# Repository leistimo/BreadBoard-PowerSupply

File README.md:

# Breadboard-Powersupply 
## Fixed 5V Power Supply
 _This linear regulated power supply accepts an input of 6V up to 35V max. The input can be either positive or negative voltage._ 

## Variable Power Supply
_This linear regulated power supply accepts an input voltage of up to 35V max. The input can be either positive or negative voltage.
To achieve a greater variable voltage at the output, the input voltage will need to be greater than the desired output but less than 35V._

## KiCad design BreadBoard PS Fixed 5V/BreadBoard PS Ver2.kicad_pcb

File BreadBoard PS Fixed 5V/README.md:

# Breadboard-Powersupply 
## Fixed 5V Power Supply
 _This linear regulated power supply accepts an input of 6V up to 35V max. The input can be either positive or negative voltage._
 https://www.digikey.com/en/mylists/list/YRKNBUZNWB

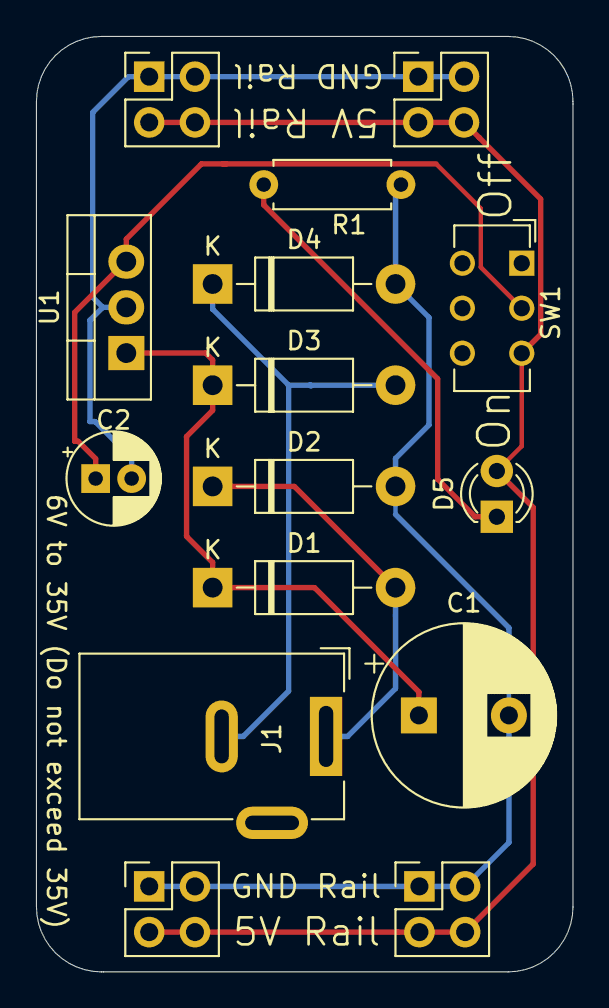
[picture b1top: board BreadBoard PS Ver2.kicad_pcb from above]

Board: 2 copper layers, 29.8 x 52.0 mm, 15 parts (0 on the bottom side), 7 nets.

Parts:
C1: 470µF; CP_Radial_D10.0mm_P5.00mm
C2: 47µF; CP_Radial_D5.0mm_P2.00mm
D1, D2, D3, D4: 1N4001; D_DO-41_SOD81_P10.16mm_Horizontal
D5: LED_GRN; LED_D3.0mm
J1: Barrel_Jack_Switch_MountingPin; BarrelJack_Wuerth_6941xx301002
J2, J3, J4, J5: Conn_02x02_Odd_Even; PinHeader_2x02_P2.54mm_Vertical
R1: 560Ω; R_Axial_DIN0207_L6.3mm_D2.5mm_P7.62mm_Horizontal
SW1: SW_DPDT_x2; SW_CuK_JS202011CQN_DPDT_Straight
U1: LM7805_TO220; TO-220-3_Vertical

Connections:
/5V: C2.1, SW1.2, U1.3
/5V-out: D5.2, J2.3, J2.4, J3.3, J3.4, J4.3, J4.4, J5.3, J5.4, SW1.3
/Gnd: C1.2, C2.2, D2.2, D4.2, J2.1, J2.2, J3.1, J3.2, J4.1, J4.2, J5.1, J5.2, R1.2, U1.2
/Vin: C1.1, D1.1, D3.1, U1.1
unnamed: D1.2, D2.1, J1.1
unnamed: D3.2, D4.1, J1.2
unnamed: D5.1, R1.1

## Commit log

2021-12-01 init ver2 files
2021-12-01 Completed Schematic
2021-12-01 added Nets & ran Electrical Rules Check
2021-12-01 Added Net List
2021-12-02 Start PCB
2021-12-02 name folder
2021-12-02 PCB wiring
2021-12-02 Add 3D Barrel Jack
2021-12-02 Run Design Rules Check
2021-12-03 Clean up PCB 3D view
2021-12-03 add logos
2021-12-06 generate gerber files
2021-12-07 add images
2021-12-07 new variable version
2021-12-07 Schematic
2021-12-07 directory fix
2021-12-08 correct C2 foot print
2021-12-08 Update C2 footprint
2021-12-08 correct C2 footprint
2021-12-08 generate gerber
2021-12-08 correct silk screen
2021-12-08 Silk Screen
2021-12-13 switcher
2021-12-19 update rail pin locations
2022-03-28 testing
2022-03-28 removed dev from main
2022-03-28 add readme to folder
2022-05-06 added video
